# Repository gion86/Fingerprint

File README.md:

# RFID Garage opener 
### RFID sensor and relay output to open a garage door upon user authentication  
**version 0.9**

This project is made of a single main C++ file and a static library and control a 
RFID reading sensor, with an Attiny84, to drive a relay contact. 
This will open/close my garage door!

The main branch contains a documentation folder with:

* the bill of material;
* datasheet of used components;
* electrical drawings;
* library source code;
* wiring notes;
* code examples;

This branch does not require any changes on hardware or schematics.

The sensor used in this code is a 125Khz RIFD module from SeeedStudio, 
http://www.seeedstudio.com/depot/125khz-rfid-module-uart-p-171.html?cPath=144_153

which reads RFID from a 20-30 mm distance and uses a particular frame format to 
send data to the controller. See the datasheet on the SeeedStudio site or in the doc
folder. 

The communication is made with the standard TTL UART serial protocol, the SoftwareSerial 
library has been used in the ATTiny.

**EEPROM tag data**

The RFID tag data are usually store in the code, but since this is a public repository,
I don't want my tags to be out in the wild.
So I made an Intel HEX compliant file with my data in plain ASCII text, which is not
versioned here. This file can be loaded on the micro EEPROM memory at every programming,
just like an EEPROM image. The AVR programmer must be configured to do that, with the 
command line parameter `Ueeprom:w:` followed by the path to the HEX file: 

Invoking: AVRDude

`/usr/bin/avrdude -pt84 -cusbasp -Uflash:w:RFID.hex:a -Ueeprom:w:/home/.../Garage_RFID/RFID/RFID.eep:a`

In the *setup()* method the micro waits for the EEPROM to be ready and then read the 
tags byte and store them in a program variable. 
Once a tag is read, the value is compared to the ones in the variable, and if the tag is 
found the relay contact is activated.

Some pictures of the original project, with fingerprint sensor, can be found at 
https://goo.gl/photos/i5Vk5WsfXXiouzTf6 .

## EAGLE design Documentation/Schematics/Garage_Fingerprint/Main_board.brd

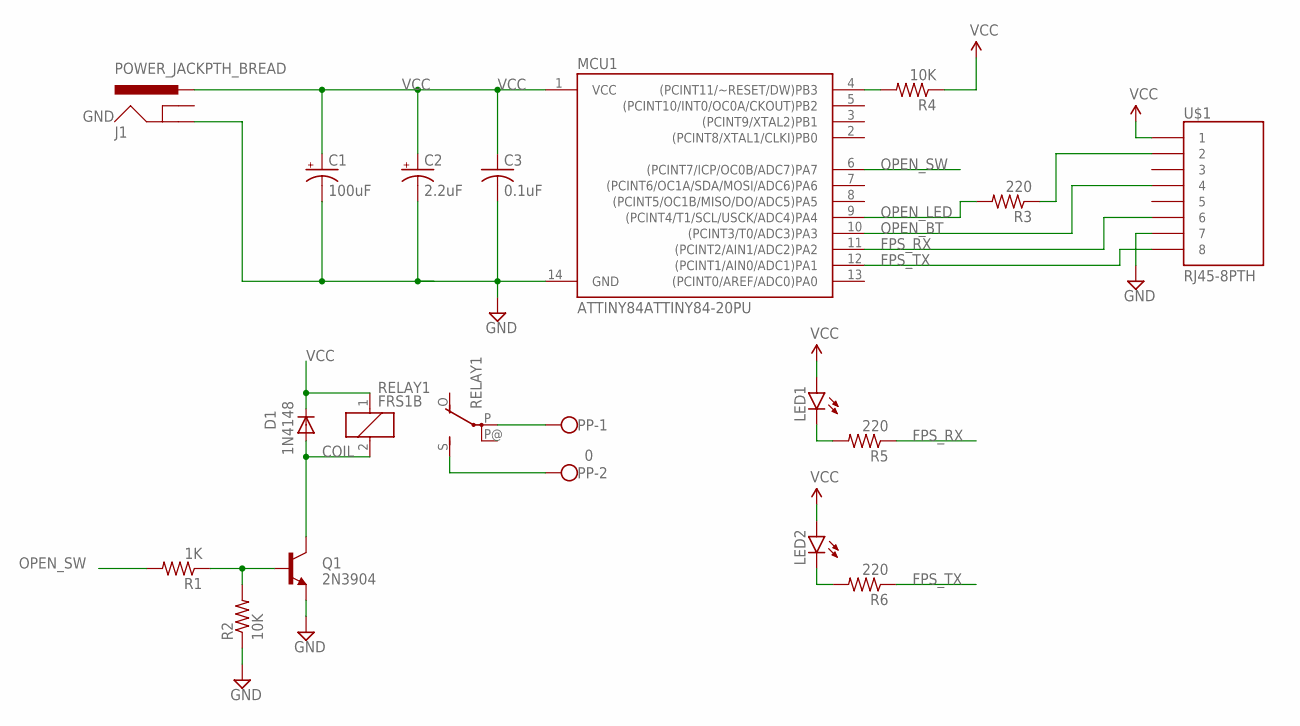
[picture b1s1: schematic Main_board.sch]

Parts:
C1: 100uF; CPOL-RADIAL-10UF-25V
C2: 2.2uF; CPOL-RADIAL-10UF-25V
C3: 0.1uF; C025-024X044
D1: 1N4148; DIODE-1N4148
J1: POWER_JACKPTH_BREAD; POWER_JACK_PTH_BREAD
LED1, LED2: LED3MM
MCU1: ATTINY84ATTINY84-20PU; DIL14
PP: 0; W237-102
Q1: 2N3904; TO-92
R1: 1K; 0207/10
R2, R4: 10K; 0207/10
R3, R5, R6: 220; 0207/10
RELAY1: FRS1B
U$1: RJ45-8PTH; RJ45-8

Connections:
COIL: D1.A, Q1.3 (C), RELAY1.2
FPS_RX: MCU1.11 ((PCINT2/AIN1/ADC2)PA2), R5.1, U$1.6
FPS_TX: MCU1.12 ((PCINT1/AIN0/ADC1)PA1), R6.1, U$1.8
GND: C1.2 (-), C2.2 (-), C3.2, J1.GND, MCU1.14 (GND), Q1.1 (E), R2.1, U$1.7
unnamed: Q1.2 (B), R1.1, R2.2
unnamed: PP.2, RELAY1.S
unnamed: PP.1, RELAY1.P
unnamed: LED2.K (C), R6.2
unnamed: MCU1.4 ((PCINT11/~RESET/DW)PB3), R4.2
unnamed: LED1.K (C), R5.2
unnamed: R3.1, U$1.2
OPEN_BT: MCU1.10 ((PCINT3/T0/ADC3)PA3), U$1.4
OPEN_LED: MCU1.9 ((PCINT4/T1/SCL/USCK/ADC4)PA4), R3.2
OPEN_SW: MCU1.6 ((PCINT7/ICP/OC0B/ADC7)PA7), R1.2
VCC: C1.1 (+), C2.1 (+), C3.1, D1.C, J1.PWR, LED1.A, LED2.A, MCU1.1 (VCC), R4.1, RELAY1.1, U$1.1

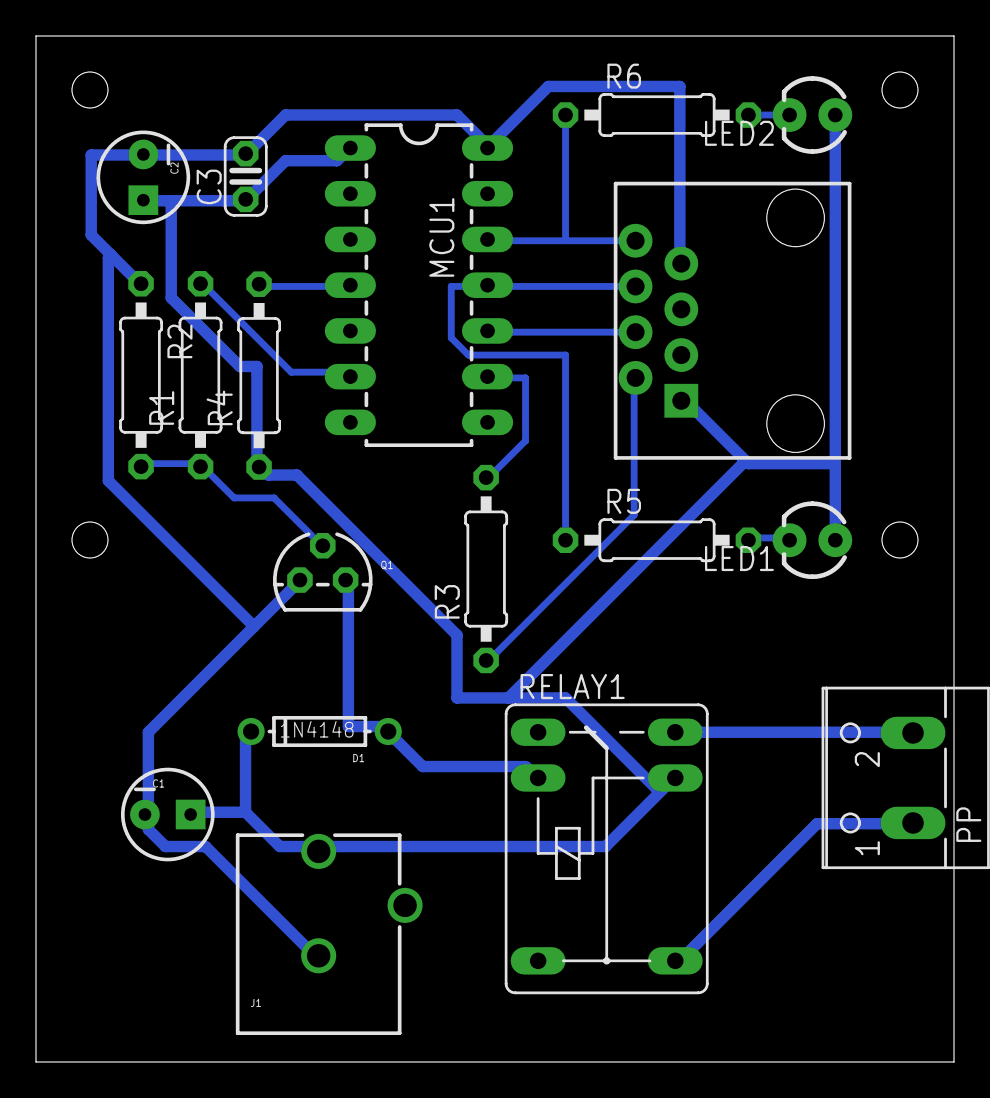
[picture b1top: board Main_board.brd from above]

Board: 2 copper layers, 51.0 x 57.0 mm, 18 parts (0 on the bottom side), 15 nets.

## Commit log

2015-10-23 Fingerprint garage opener: first import of FPS_GT511C1R sensor library . Full credit to Josh Hawley for the library.
2015-10-23 Added readme and license
2015-10-23 Added a state to identify fingerprint. Added comments and safety checks.
2015-10-23 Enabled serial debug only on some functions, to keep the final elf image small to fit in the micro.
2015-10-25 Added serial debug to main. Refactored projects configuration to compile for differente CPU targets. Added makefile and updated readme.
2015-10-25 Commented out Serial print in SendCommand function: the print caused problems if UseSerialDebug = true!! Refactored projects configuration to compile for differente CPU targets.
2015-10-25 Removed useless readme and license file
2015-10-25 Update version
2015-11-01 Added PinMode configuration in setup. Version 0.9 ready for final test!!
2015-11-04 Added fps.IsPressFinger() on authentication step, to improve verification performance (stay active until the finger is released)
2015-11-04 Updated README and INSTALL
2015-11-07 Reverted back to one single step to authenticate, after some additional test the fingerprint sensor is working better and faster if using a delay of about 100ms between isPressFinger() calls. Changed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
2015-11-08 Added Documentation folder with datasheets, schematic, bill of material..
2015-11-08 modified readme
2015-11-22 Deleted fingerprint database and added to ignore
2015-11-29 Added binaries to ignore, modifiied debug info in main, deleted unused datasheets
2015-11-29 Modified ignore with wildcards
2016-01-09 First import for new RIFD branch
2016-01-10 First commit for SeeedRFID library, modified to work with model RFR101A1M from SeeedStudio: tag value retain (in RAM), binary data validation and checksum verification added.
2016-01-10 First commit with working code: main.cpp and an external file (Intel HEX format, not versioned) to upload the EEPROM image. The RFID tag to compare against will be loaded from EEPROM.
2016-01-10 Updated version
2016-01-10 Library README to be completed
2016-01-10 First version of project README
2016-01-12 New more robust "while" cycle to read from serial from start byte to end byte (2 - 3 in datasheet)
2016-01-12 Added documentation folder with RFID sensor datasheet. Therest of hardware is the same as fingerprint branch
2016-01-12 Added macro to set/reset register flag for PCINT interrupt
2016-01-12 Added file to gitignore
2016-01-13 Updated version to 0.9
2016-01-13 Renamed SeeedStudio folder, updated makefile with project library
2016-01-23 Removed wrong project reference
2016-03-13 Added project reference: SeedRFID library
2016-12-18 Reorganization of cores and library: changed projects includes and link folder. Removed library since it will move to a different repo.
2016-12-18 Added sensor image
2017-10-08 Moved library project to a different repo.
2018-04-30 Moved some components datasheet into new repo

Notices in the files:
parts and their libraries:
SparkFun-Capacitors: Licensing: Creative Commons ShareAlike 4.0 International - https://creativecommons.org/licenses/by-sa/4.0
